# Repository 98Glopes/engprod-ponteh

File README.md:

# engprod-ponteh
Repositório criado para a disciplina de engenharia de produto

## Objetivo

Desenvolver uma placa microcontrolada capaz de controlar 2 motores de
corrente continua, a placa deve conter botões para o comando dos motores, e
obrigatoriamente deve conter um botão de emergência que pare os dois motores
assim que for pressionado.

## Conteúdo

* Firmware para Atmega328p
* PCI feita no software Eagle

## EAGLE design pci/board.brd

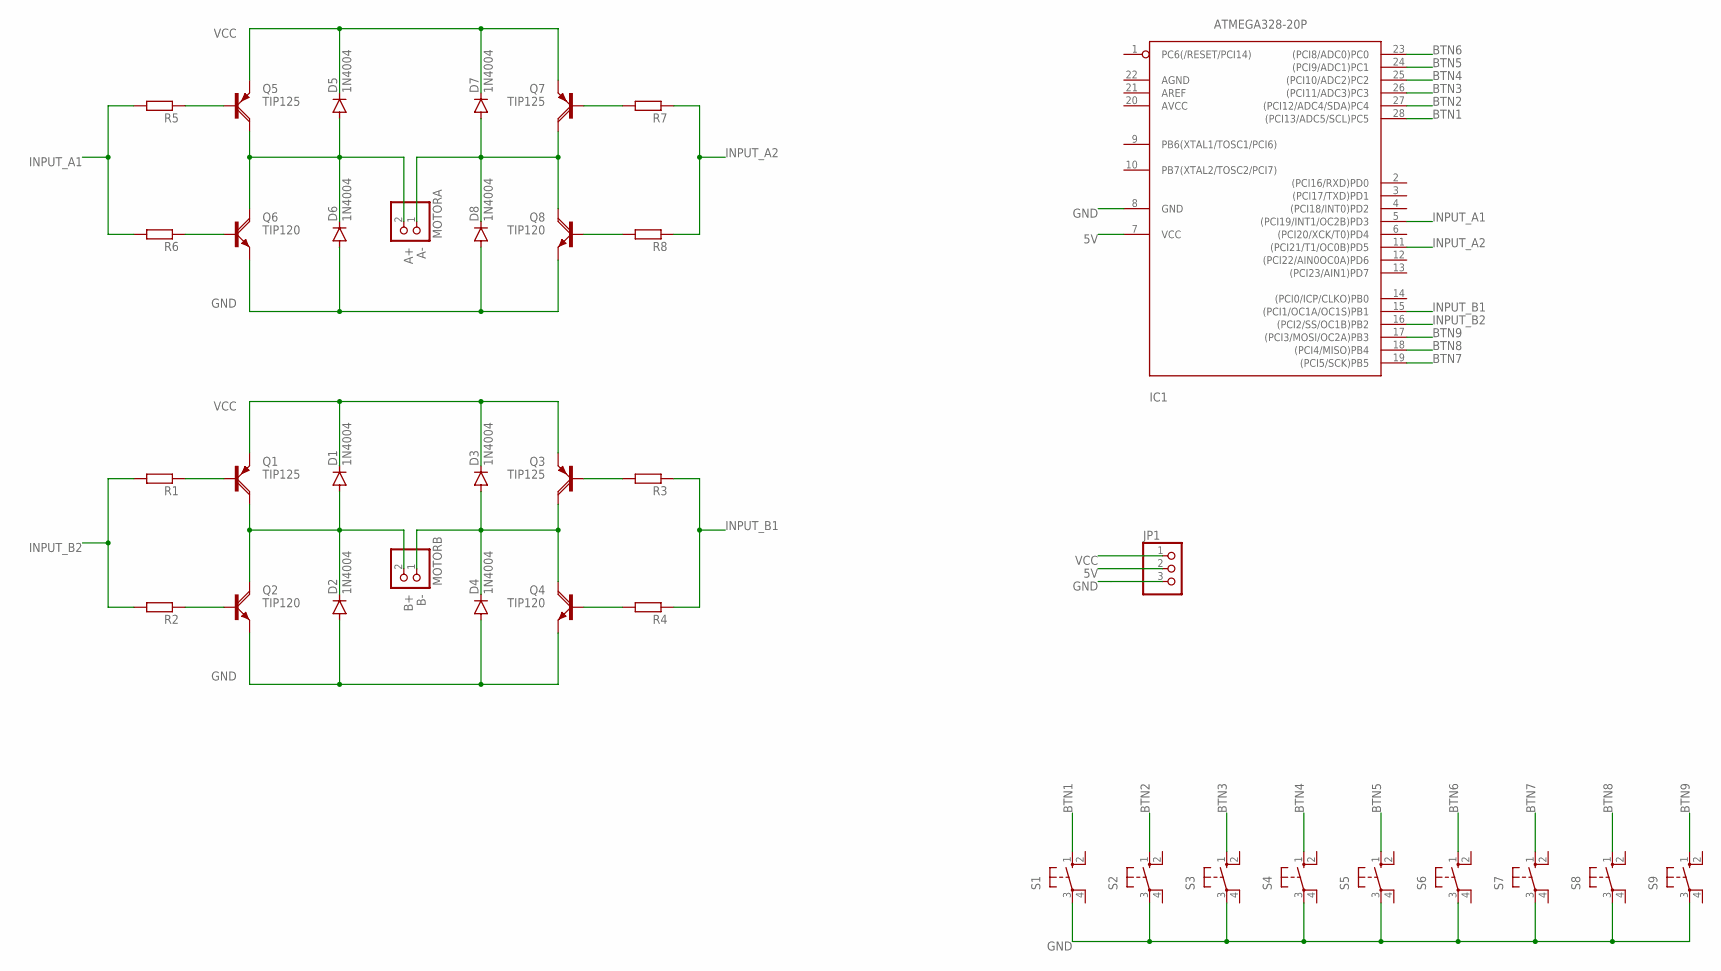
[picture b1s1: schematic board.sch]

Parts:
D1, D2, D3, D4, D5, D6, D7, D8: 1N4004; DO41-10
IC1: ATMEGA328-20P; DIL28-3
JP1: PINHD-1X3; 1X03
MOTORA: PINHD-1X2; 1X02
MOTORB: PINHD-1X2; 1X02
Q1, Q3, Q5, Q7: TIP125; TO220AH
Q2, Q4, Q6, Q8: TIP120; TO220AH
R1, R2, R3, R4, R5, R6, R7, R8: R-EU_0204/7; 0204/7
S1, S2, S3, S4, S5, S6, S7, S8, S9: 10-XX; B3F-10XX

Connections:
5V: IC1.7 (VCC), JP1.2
A+: D5.A, D6.C, MOTORA.2, Q5.C, Q6.C
A-: D7.A, D8.C, MOTORA.1, Q7.C, Q8.C
B+: D1.A, D2.C, MOTORB.2, Q1.C, Q2.C
B-: D3.A, D4.C, MOTORB.1, Q3.C, Q4.C
BTN1: IC1.28 ((PCI13/ADC5/SCL)PC5), S1.1 (S)
BTN2: IC1.27 ((PCI12/ADC4/SDA)PC4), S2.1 (S)
BTN3: IC1.26 ((PCI11/ADC3)PC3), S3.1 (S)
BTN4: IC1.25 ((PCI10/ADC2)PC2), S4.1 (S)
BTN5: IC1.24 ((PCI9/ADC1)PC1), S5.1 (S)
BTN6: IC1.23 ((PCI8/ADC0)PC0), S6.1 (S)
BTN7: IC1.19 ((PCI5/SCK)PB5), S7.1 (S)
BTN8: IC1.18 ((PCI4/MISO)PB4), S8.1 (S)
BTN9: IC1.17 ((PCI3/MOSI/OC2A)PB3), S9.1 (S)
GND: D2.A, D4.A, D6.A, D8.A, IC1.8 (GND), JP1.3, Q2.E, Q4.E, Q6.E, Q8.E, S1.3, S2.3, S3.3, S4.3, S5.3, S6.3, S7.3, S8.3, S9.3
INPUT_A1: IC1.5 ((PCI19/INT1/OC2B)PD3), R5.2, R6.2
INPUT_A2: IC1.11 ((PCI21/T1/OC0B)PD5), R7.1, R8.1
INPUT_B1: IC1.15 ((PCI1/OC1A/OC1S)PB1), R3.1, R4.1
INPUT_B2: IC1.16 ((PCI2/SS/OC1B)PB2), R1.2, R2.2
unnamed: Q2.B, R2.1
unnamed: Q1.B, R1.1
unnamed: Q6.B, R6.1
unnamed: Q3.B, R3.2
unnamed: Q4.B, R4.2
unnamed: Q5.B, R5.1
unnamed: Q7.B, R7.2
unnamed: Q8.B, R8.2
VCC: D1.C, D3.C, D5.C, D7.C, JP1.1, Q1.E, Q3.E, Q5.E, Q7.E

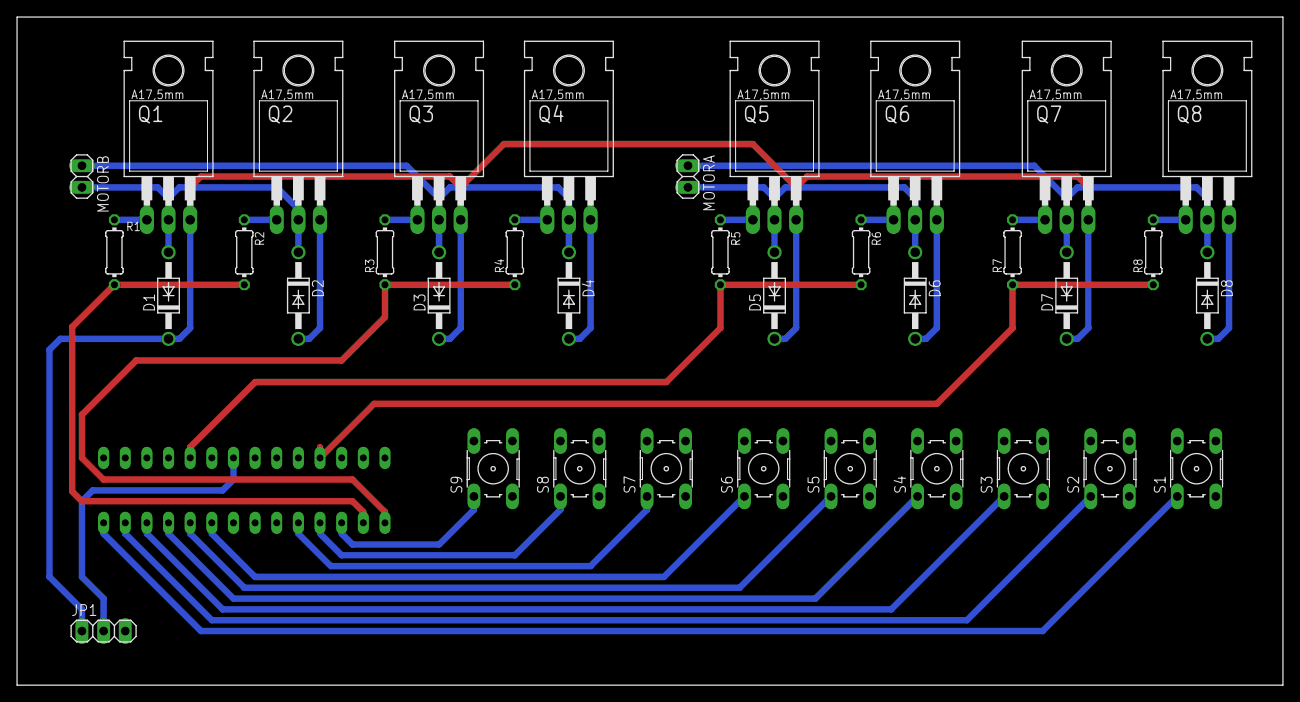
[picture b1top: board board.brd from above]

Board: 2 copper layers, 148.6 x 78.4 mm, 37 parts (1 on the bottom side), 28 nets.

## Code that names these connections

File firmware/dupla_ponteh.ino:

#define BTN1 0  //liga motor A / Desliga motor A
#define BTN2 1  //Inverte motor A / Inverte Motor A
#define BTN3 2  //Aumenta velocidade do motor A
#define BTN4 3  //Diminui velocidade do motor A
#define BTN5 4  //Liga motor B / Desliga Motor B
#define BTN6 5  //Inverte motor B / Inverte motor B
#define BTN7 6  //Aumenta velocidade motor B
#define BTN8 7  //Diminui velocidade motor B
#define BTN9 8  //Emergencia - desliga os dois motores

#define INPUT_A1 3
#define INPUT_A2 5

#define INPUT_B1 9
#define INPUT_B2 10


//matriz para guardar estado dos botoes
bool state_btn[8] = {1, 1, 1, 1, 1, 1, 1, 1};
bool last_state[8] = {1, 1, 1, 1, 1, 1, 1, 1};


//Matriz com os pinos referentes aos botões
//Segue a ordem BTN1, BTN2, ... , BTN9;
int pins_btn[8] = {19, 18, 17, 16, 15, 14, 11, 12};




//Struct para guardar as informaçoes de cada motor
struct motores {

  bool state;
  char dir;
  int vel;
};

//Cria uma struct para cada motor
motores motor_a = {0, 'e', 20};
motores motor_b = {0, 'e', 20};


void setup() {
  // configura todos os pinos de entrada usando um loop
  for (int i = 0; i < 8; i++) {
    pinMode(pins_btn[i], INPUT_PULLUP);
  } 

  //Associa uma interrupção ao BTN9
  //Configura a interrupção para borda de descida
  attachInterrupt(digitalPinToInterrupt(BTN9), emergencia, FALLING);

  //Configura as saidas analogicas
  pinMode(INPUT_A1, OUTPUT);
  pinMode(INPUT_A2, OUTPUT);
  pinMode(INPUT_B1, OUTPUT);
  pinMode(INPUT_B2, OUTPUT);

}

void loop() {
  //Escaneia todas os botoes utilizando um loop
  for (int i = 0; i < 8; i++) {
    state_btn[i] = digitalRead(pins_btn[i]);
  }

  //liga o motor A
  //utiliza como referencia o ultimo estado pra criar um detector de
  //borda de decidaa, o mesmo conceito é utilizado para todos os outros botoes
  //Para as demais funções, necessita que o estado do motor seja ligado (1)
  if (last_state[BTN1] == 1 && state_btn[BTN1] == 0) {

    //liga ou desliga o motor dependendo do estado atual
    if (motor_a.state == 1) {
      //desliga
      digitalWrite(INPUT_A1, 0);
      digitalWrite(INPUT_A2, 0);
      motor_a.state = 0;
    } else {
      //liga com a velocidade minima
      //Verifica a direção do motor para acionar o PWM correto
      motor_a.state = 1;
      if (motor_a.dir == 'e') {

        digitalWrite(INPUT_A1, 0);
        analogWrite(INPUT_A2, motor_a.vel);
      } else {

        digitalWrite(INPUT_A1, motor_a.vel);
        analogWrite(INPUT_A2, 1);
      }
    }
  }

  //Inverte a rotação do motor
  if (last_state[BTN2] == 1 && state_btn[BTN2] == 0 && motor_a.state == 1) {

    //inverte o sentido de rotação dos motores
    if (motor_a.dir == 'd') {
      digitalWrite(INPUT_A1, 0);
      analogWrite(INPUT_A2, motor_a.dir);
      motor_a.dir = 'e';
    } else {
      analogWrite(INPUT_A1, motor_a.dir);
      digitalWrite(INPUT_A2, 0);
      motor_a.dir = 'd';

    }
  }

  //Aumenta velocidade do motor
  if (last_state[BTN3] == 1 && state_btn[BTN3] == 0 && motor_a.state == 1) {

    motor_a.vel += 10;
    //Verifica se a velocidade é maior que 255
    if (motor_a.vel > 255)
      motor_a.vel = 255;

    if (motor_a.dir == 'e') {
      digitalWrite(INPUT_A1, 0);
      analogWrite(INPUT_A2, motor_a.vel);
    } else {
      analogWrite(INPUT_A1, motor_a.vel);
      digitalWrite(INPUT_A2, 0);
    }

  }

  //Diminui a velocidade do motor
  if (last_state[BTN4] == 1 && state_btn[BTN4] == 0 && motor_a.state == 1) {

    motor_a.vel -= 10;
    //Verifica se a velocidade é menor que 20
    if (motor_a.vel < 20)
      motor_a.vel = 255;

    if (motor_a.dir == 'e') {
      digitalWrite(INPUT_A1, 0);
      analogWrite(INPUT_A2, motor_a.vel);
    } else {
      analogWrite(INPUT_A1, motor_a.vel);
      digitalWrite(INPUT_A2, 0);
    }

  }

  //Liga o motor
  if (last_state[BTN5] == 1 && state_btn[BTN5] == 0) {

    //liga ou desliga o motor dependendo do estado atual
    if (motor_b.state == 1) {
      //desliga
      digitalWrite(INPUT_B1, 0);
      digitalWrite(INPUT_B2, 0);
      motor_b.state = 0;
    } else {
      //liga com a velocidade minima
      //Verifica a direção do motor para acionar o PWM correto
      motor_b.state = 1;
      if (motor_b.dir == 'e') {

        digitalWrite(INPUT_B1, 0);
        analogWrite(INPUT_B2, motor_b.vel);
      } else {

        digitalWrite(INPUT_B1, motor_b.vel);
        analogWrite(INPUT_B2, 1);
      }
    }
  }

  //Inverte a rotação do motor
  if (last_state[BTN6] == 1 && state_btn[BTN6] == 0 && motor_b.state == 1) {

    //inverte o sentido de rotação dos motores
    if (motor_b.dir == 'd') {
      digitalWrite(INPUT_B1, 0);
      analogWrite(INPUT_B2, motor_b.dir);
      motor_b.dir = 'e';
    } else {
      analogWrite(INPUT_B1, motor_b.dir);
      digitalWrite(INPUT_B2, 0);
      motor_b.dir = 'd';

    }
  }

  //Aumenta velocidade do motor
  if (last_state[BTN7] == 1 && state_btn[BTN7] == 0 && motor_b.state == 1) {

    motor_b.vel += 10;
    //Verifica se a velocidade é maior que 255
    if (motor_b.vel > 255)
      motor_b.vel = 255;

    if (motor_b.dir == 'e') {
      digitalWrite(INPUT_B1, 0);
      analogWrite(INPUT_B2, motor_b.vel);
    } else {
      analogWrite(INPUT_B1, motor_b.vel);
      digitalWrite(INPUT_B2, 0);
    }

  }

  //Diminui a velocidade do motor
  if (last_state[BTN8] == 1 && state_btn[BTN8] == 0 && motor_b.state == 1) {

    motor_b.vel -= 10;
    //Verifica se a velocidade é menor que 20
    if (motor_b.vel < 20)
      motor_b.vel = 255;

    if (motor_b.dir == 'e') {
      digitalWrite(INPUT_B1, 0);
      analogWrite(INPUT_B2, motor_b.vel);
    } else {
      analogWrite(INPUT_B1, motor_b.vel);
      digitalWrite(INPUT_B2, 0);
    }

  }

  //Atualiza a matriz last_state
  for (int i=0; i < 8; i++){
    last_state[i] = state_btn[i];
  }
}
//Função de emergencia executada na interrupção
void emergencia(void){
  //Para os dois motores ao mesmo tempo

  //Para o motor A
      digitalWrite(INPUT_A1, 0);
      digitalWrite(INPUT_A2, 0);
  
  //Para o motor B
      digitalWrite(INPUT_B1, 0);
      digitalWrite(INPUT_B2, 0);
  
}

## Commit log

2019-11-18 Atualizado readme.md
2019-11-18 Adcionado PCI
2019-11-18 Adcionado código para atmega328p
